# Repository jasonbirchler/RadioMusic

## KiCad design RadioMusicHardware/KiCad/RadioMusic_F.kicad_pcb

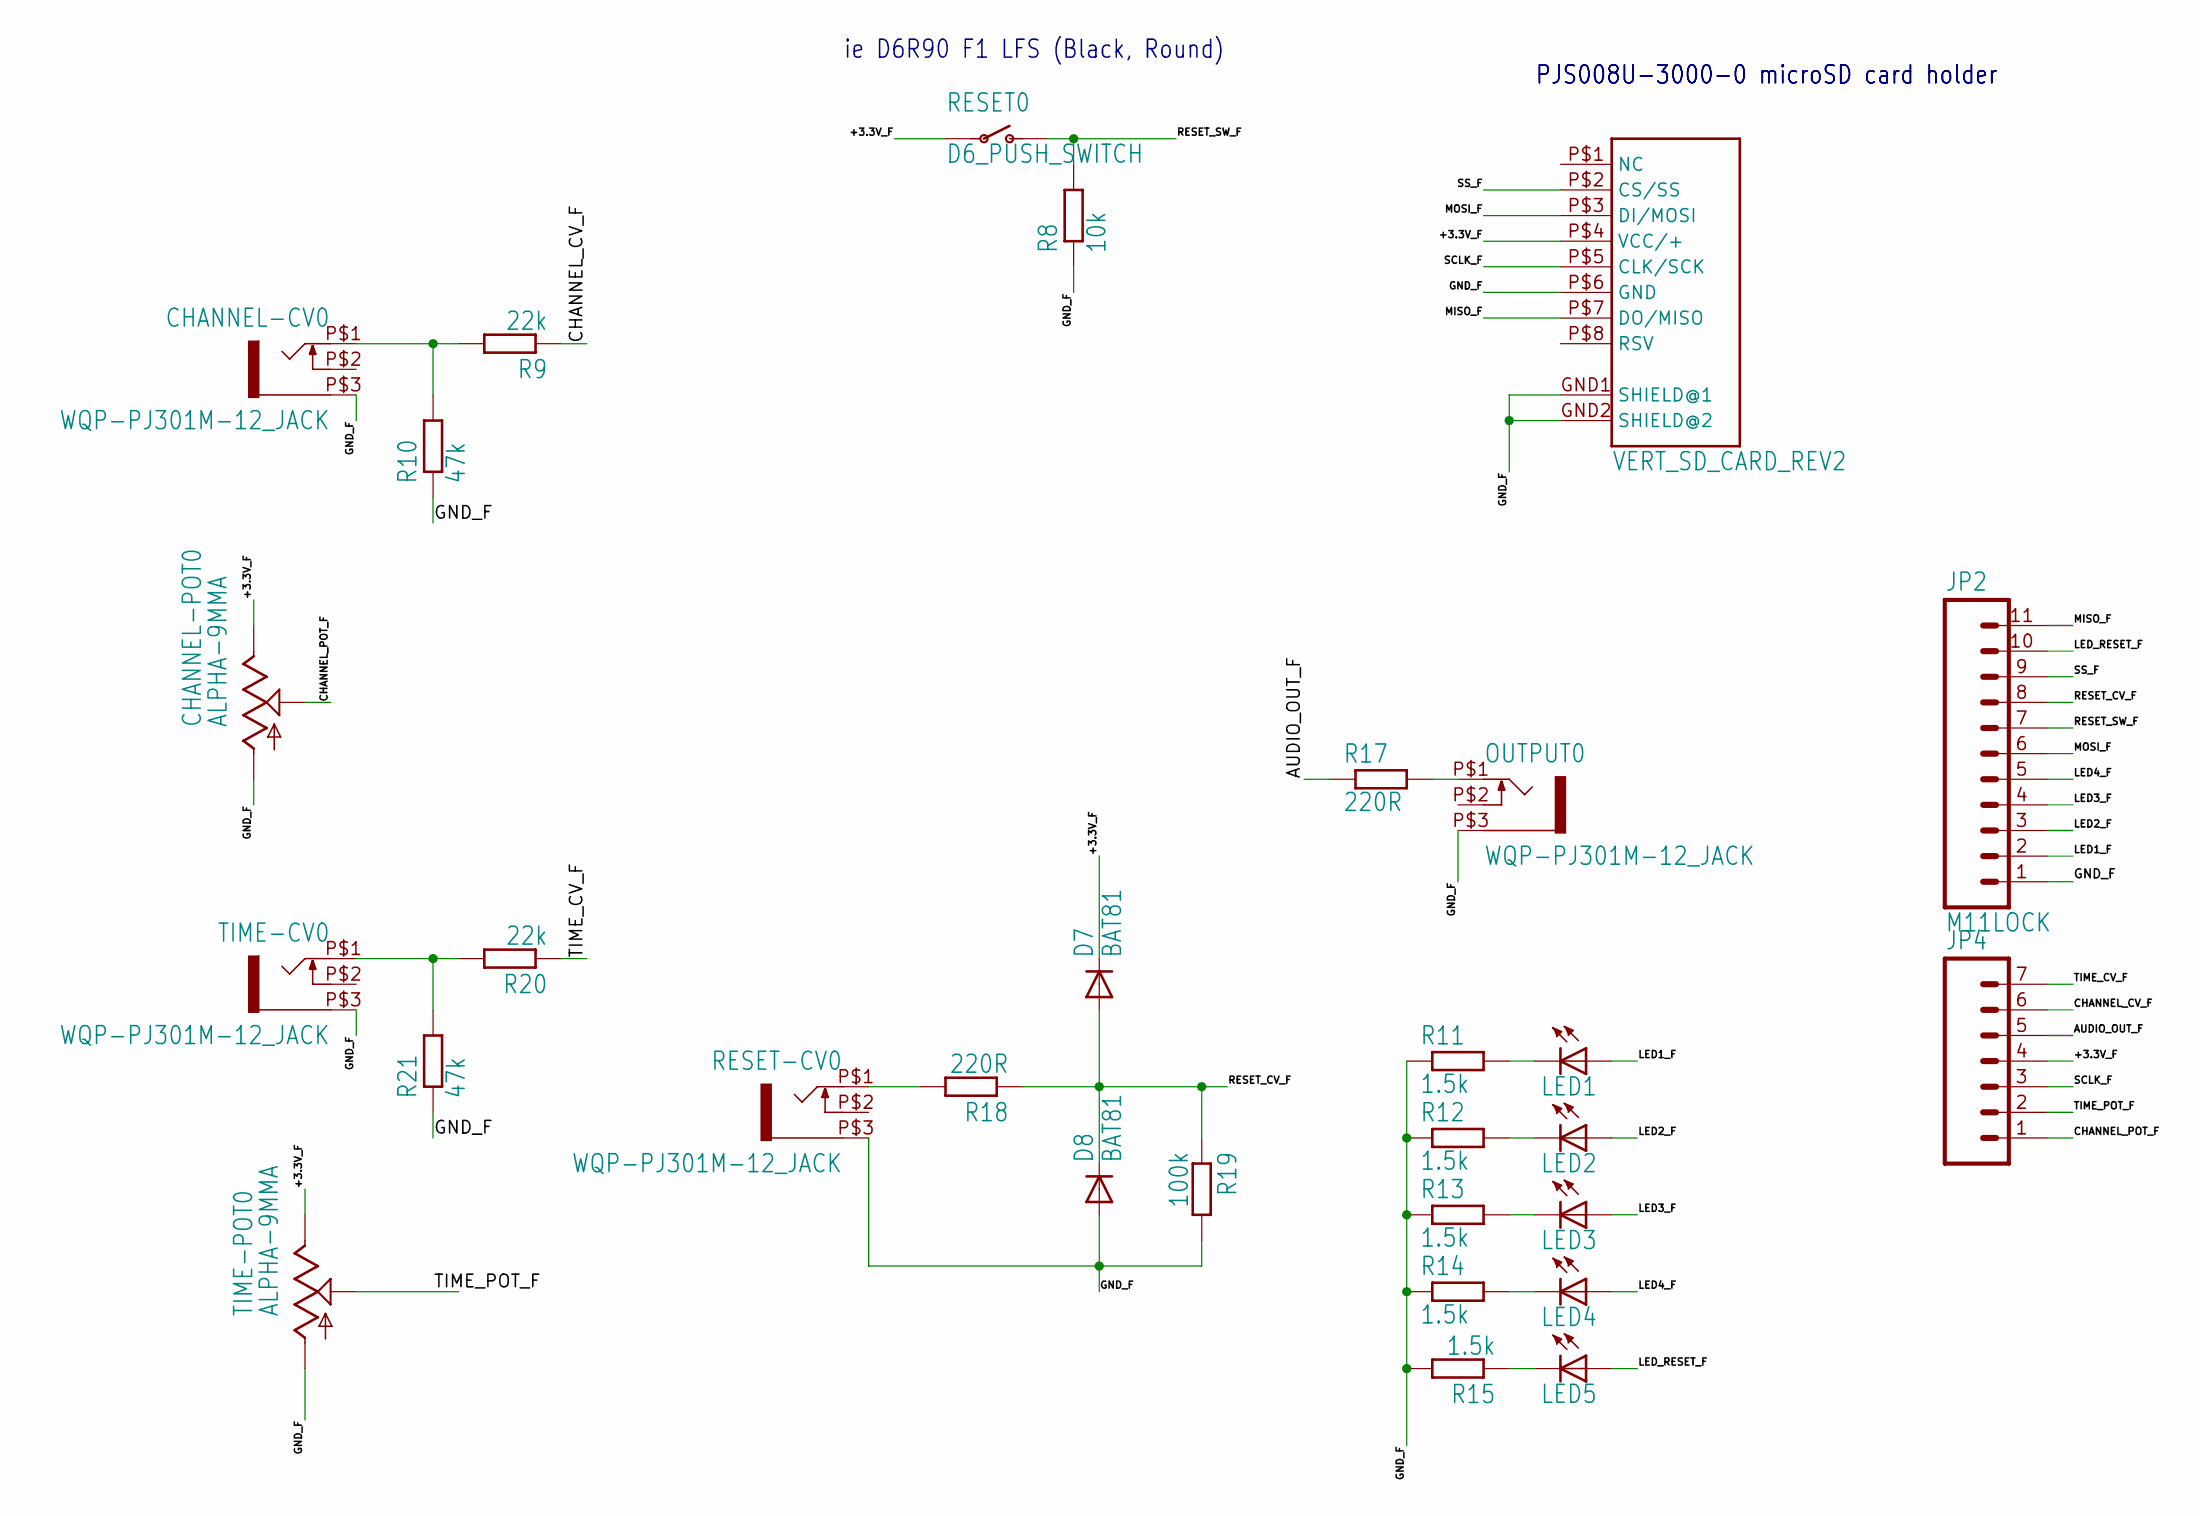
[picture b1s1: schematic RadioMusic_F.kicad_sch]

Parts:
CHANNEL-CV0: WQP-PJ301M-12_JACK
CHANNEL-POT0: ALPHA-9MMA; EVUF
D7, D8: BAT81; DO34-7
JP2: M11LOCK; 1X11_LOCK
JP4: M07LOCK; 1X07_LOCK
LED1, LED2, LED3, LED4, LED5: LED3MM
OUTPUT0: WQP-PJ301M-12_JACK
R8: 10k; 0207_10
R9, R20: 22k; 0207_10
R10, R21: 47k; 0207_10
R11, R12, R13, R14, R15: 1.5k; 0207_10
R17, R18: 220R; 0207_10
R19: 100k; 0207_10
RESET0: D6_PUSH_SWITCH; D6_BUTTON_RND
RESET-CV0: WQP-PJ301M-12_JACK
TIME-CV0: WQP-PJ301M-12_JACK
TIME-POT0: ALPHA-9MMA; EVUF
X1: VERT_SD_CARD_REV2; VERT_MICROSD_REV2

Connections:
+3.3V_F: CHANNEL-POT0.3 (E), D7.C, JP4.4, RESET0.P$3, RESET0.P$4, TIME-POT0.3 (E), X1.P$4 (VCC/+)
AUDIO_OUT_F: JP4.5, R17.1
CHANNEL_CV_F: JP4.6, R9.1
CHANNEL_POT_F: CHANNEL-POT0.2 (S), JP4.1
GND_F: CHANNEL-CV0.P$3 (1), CHANNEL-POT0.1 (A), D8.A, JP2.1, OUTPUT0.P$3 (1), R8.1, R10.1, R11.1, R12.1, R13.1, R14.1, R15.2, R19.2, R21.1, RESET-CV0.P$3 (1), TIME-CV0.P$3 (1), TIME-POT0.1 (A), X1.GND1 (SHIELD@1), X1.GND2 (SHIELD@2), X1.P$6 (GND)
LED1_F: JP2.2, LED1.A
LED2_F: JP2.3, LED2.A
LED3_F: JP2.4, LED3.A
LED4_F: JP2.5, LED4.A
LED_RESET_F: JP2.10, LED5.A
MISO_F: JP2.11, X1.P$7 (DO/MISO)
MOSI_F: JP2.6, X1.P$3 (DI/MOSI)
unnamed: OUTPUT0.P$1 (2), R17.2
unnamed: CHANNEL-CV0.P$1 (2), R9.2, R10.2
unnamed: R18.2, RESET-CV0.P$1 (2)
unnamed: LED1.K (C), R11.2
unnamed: LED2.K (C), R12.2
unnamed: LED3.K (C), R13.2
unnamed: LED4.K (C), R14.2
unnamed: LED5.K (C), R15.1
RESET_CV_F: D7.A, D8.C, JP2.8, R18.1, R19.1
RESET_SW_F: JP2.7, R8.2, RESET0.P$1 (O), RESET0.P$2 (O)
SCLK_F: JP4.3, X1.P$5 (CLK/SCK)
SS_F: JP2.9, X1.P$2 (CS/SS)
TEMP: R20.2, R21.2, TIME-CV0.P$1 (2)
TIME_CV_F: JP4.7, R20.1
TIME_POT_F: JP4.2, TIME-POT0.2 (S)

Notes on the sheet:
PJS008U-3000-0 microSD card holder
ie D6R90 F1 LFS (Black, Round)

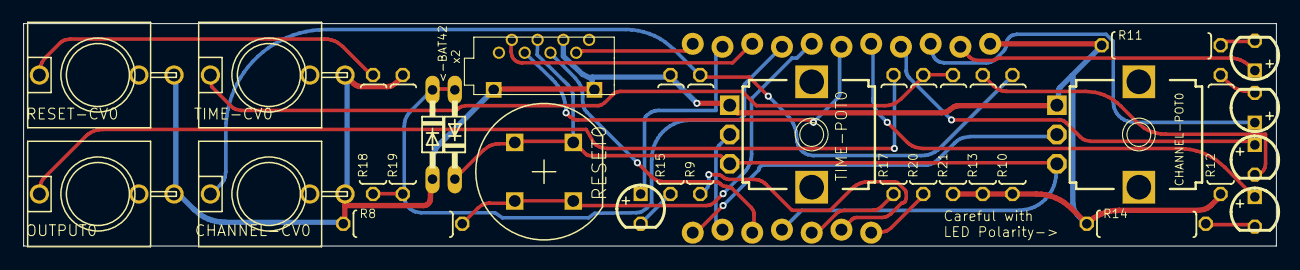
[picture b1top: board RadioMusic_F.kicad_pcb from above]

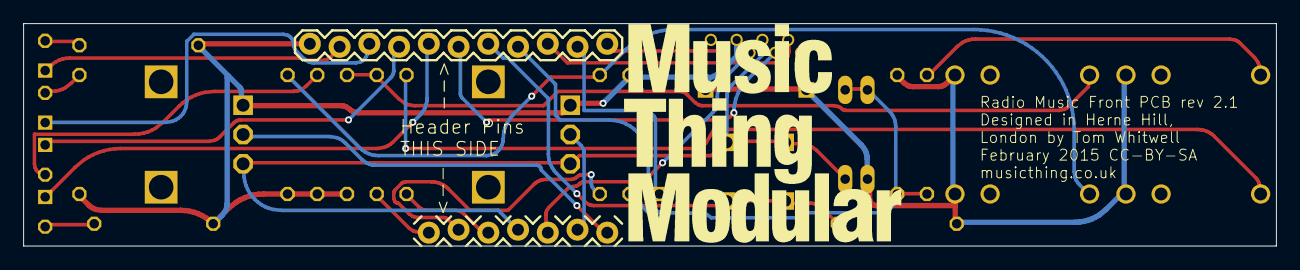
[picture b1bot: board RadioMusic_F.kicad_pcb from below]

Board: 4 copper layers, 107.0 x 19.0 mm, 31 parts (3 on the bottom side), 27 nets.

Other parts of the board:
U$1: MTM_2CM

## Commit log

2025-01-19 first attempt at converting to kicad

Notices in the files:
RadioMusicHardware/KiCad/RadioMusic_F.kicad_pcb:
February 2015 CC-BY-SA
